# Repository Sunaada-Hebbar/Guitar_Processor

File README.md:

The objective of the project is to develop a microprocessor(Odroid C2) based system which has an initial analog circuit stage that takes input from an electric guitar (analog audio signals), pre amplifies it and applies antialias filter and then the processed signal is given as input to Odroid C2 ADC. The digital signals received are passed through various DSP filters/algorithms through a software application running on Odroid C2 to provide various audio effects (produced by typical guitar processor in the market) and the output digital signal is converted back to the analog signal by a final output stage which can be fed to a guitar amplifier.

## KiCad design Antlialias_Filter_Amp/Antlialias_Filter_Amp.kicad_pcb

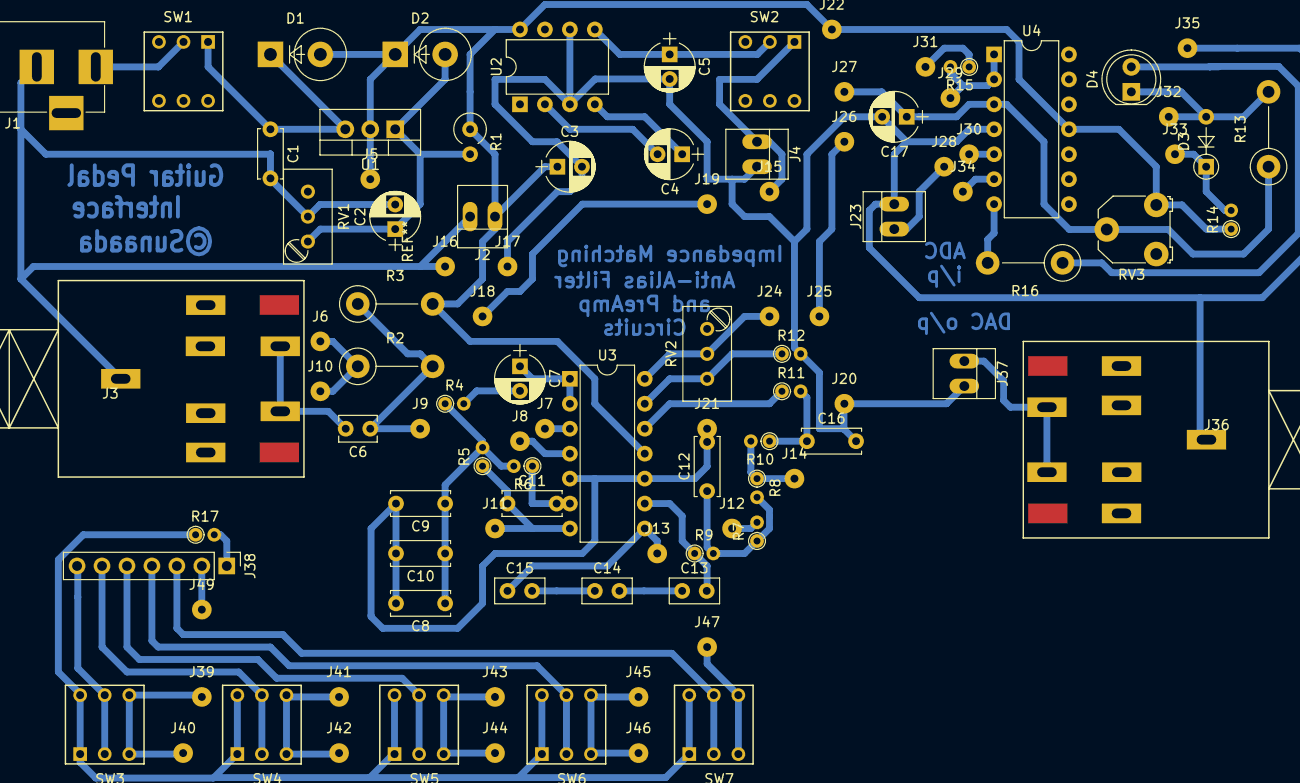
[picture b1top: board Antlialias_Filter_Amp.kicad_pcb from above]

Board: 2 copper layers, 100 parts (0 on the bottom side), 39 nets.

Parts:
C1: C; C_Disc_D5.0mm_W2.5mm_P5.00mm
C2: CP_Small; CP_Radial_D5.0mm_P2.50mm
C3, C4, C5, C7, C17: CP; CP_Radial_D5.0mm_P2.50mm
C6: C; C_Disc_D3.8mm_W2.6mm_P2.50mm
C8, C9, C10, C11, C12, C16: C; C_Disc_D6.0mm_W2.5mm_P5.00mm
C13, C14, C15: C; C_Disc_D5.0mm_W2.5mm_P2.50mm
D1, D2: D; D_DO-201_P5.08mm_Vertical_KathodeUp
D3: D_Zener; D_DO-35_SOD27_P5.08mm_Vertical_AnodeUp
D4: LED; LED_D5.0mm
J1: BARREL_JACK
J2, J4, J23, J37: CONN_01X02; PINHEAD1-2
J3, J36: JACK_TRS_6PINS; Audio_Jack
J5, J6, J7, J8, J9, J10, J11, J12, J13, J14, J15, J16, J17, J18, J19, J20, J21, J22, J24, J25, J26, J27, J28, J29, J30, J31, J32, J33, J34, J35, J39, J40, J41, J42, J43, J44, J45, J46, J47, J49: CONN_01X01; SolderWirePad_single_0-8mmDrill
J38: CONN_01X07; Pin_Header_Straight_1x07_Pitch2.54mm
R1: R; R_Axial_DIN0309_L9.0mm_D3.2mm_P2.54mm_Vertical
R2, R3, R13, R16: R; R_Axial_DIN0411_L9.9mm_D3.6mm_P7.62mm_Vertical
R4, R5, R6, R7, R8, R9, R10, R11, R12, R14, R15, R17: R; R_Axial_DIN0204_L3.6mm_D1.6mm_P1.90mm_Vertical
RV1, RV2: POT_TRIM; Potentiometer_Trimmer_Bourns_3296W
RV3: POT_TRIM; Potentiometer_Triwood_RM-065
SW1, SW2: R; SW_PUSH_x2
SW3, SW4, SW5, SW6, SW7: SW; SW_PUSH_x2
U1: LM317T; TO-220_Vertical
U2: TC7660; DIP-8_W7.62mm
U3: OPA4228; DIP-14_W7.62mm
U4: LM324; DIP-14_W7.62mm

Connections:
GNDREF: C1.2, C2.2, C3.2, C5.2, C8.2, C9.2, C10.2, C12.2, C16.2, C17.2, D3.2, D4.1, J1.2, J2.2, J3.1, J4.2, J16.1, J17.1, J20.1, J21.1, J23.2, J32.1, J35.1, J36.1, J37.2, R12.2, R13.2, RV1.2, U2.3, U2.6, U3.5, U3.10, U4.4
unnamed: C1.1, D1.1, SW1.1, U1.3
unnamed: C2.1, D2.2, R1.2, RV1.1, U1.1
unnamed: C4.1, U2.4
unnamed: C4.2, U2.2
unnamed: C5.1, SW2.2, U2.5
unnamed: C6.1, J7.1, J9.1, R2.2, R3.1, U3.3
unnamed: C6.2, J3.2, J3.3
unnamed: C7.1, U3.1, U3.2
unnamed: C7.2, R4.2
unnamed: C8.1, C9.1, C10.1, R4.1, R5.2, R6.2
unnamed: C11.1, J11.1, J12.1, R5.1, R7.2, U3.7
unnamed: C11.2, R6.1, U3.6
unnamed: C12.1, R7.1, R8.2, R9.2
unnamed: C13.1, C14.2
unnamed: C13.2, R9.1, U3.9
unnamed: C14.1, C15.2
unnamed: C15.1, J13.1, J14.1, R8.1, R10.2, U3.8
unnamed: C16.1, R10.1, R11.2
unnamed: C17.1, J24.1, J25.1, J26.1, J27.1, R13.1, RV2.2, RV3.2, U3.14, U4.3
unnamed: D3.1, J33.1, J34.1, R14.2, U4.6
unnamed: D4.2, R16.1
unnamed: J1.1, SW1.2
unnamed: J23.1, J28.1, J29.1, R15.2, U4.1, U4.2
unnamed: J30.1, J31.1, R15.1, U4.5
unnamed: J36.2, J36.3, J37.1
unnamed: J38.1, R17.2
unnamed: J38.2, J39.1, J40.1, J41.1, J42.1, J43.1, J44.1, J45.1, J46.1, J47.1, J49.1, SW3.3, SW3.4, SW4.3, SW4.4, SW5.3, SW5.4, SW6.3, SW6.4, SW7.3, SW7.4
unnamed: J38.3, SW7.2, SW7.5
unnamed: J38.4, SW6.2, SW6.5
unnamed: J38.5, SW5.2, SW5.5
unnamed: J38.6, SW4.2, SW4.5
unnamed: J38.7, SW3.2, SW3.5
unnamed: R11.1, U3.12
unnamed: R12.1, RV2.3, U3.13
unnamed: R16.2, U4.7
unnamed: R17.1, SW3.1, SW3.6, SW4.1, SW4.6, SW5.1, SW5.6, SW6.1, SW6.6, SW7.1, SW7.6
VCC: C3.1, D1.2, D2.1, J2.1, J5.1, J22.1, R1.1, R3.2, R14.1, RV3.3, U1.2, U2.8, U3.11, U4.11
VEE: J4.1, J6.1, J8.1, J10.1, J15.1, J18.1, J19.1, R2.1, SW2.1, U3.4

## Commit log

2017-05-14 HW Design Files
2017-05-14 Data sheets of HW components

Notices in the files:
Antlialias_Filter_Amp/Antlialias_Filter_Amp.kicad_pcb:
©Sunaada
